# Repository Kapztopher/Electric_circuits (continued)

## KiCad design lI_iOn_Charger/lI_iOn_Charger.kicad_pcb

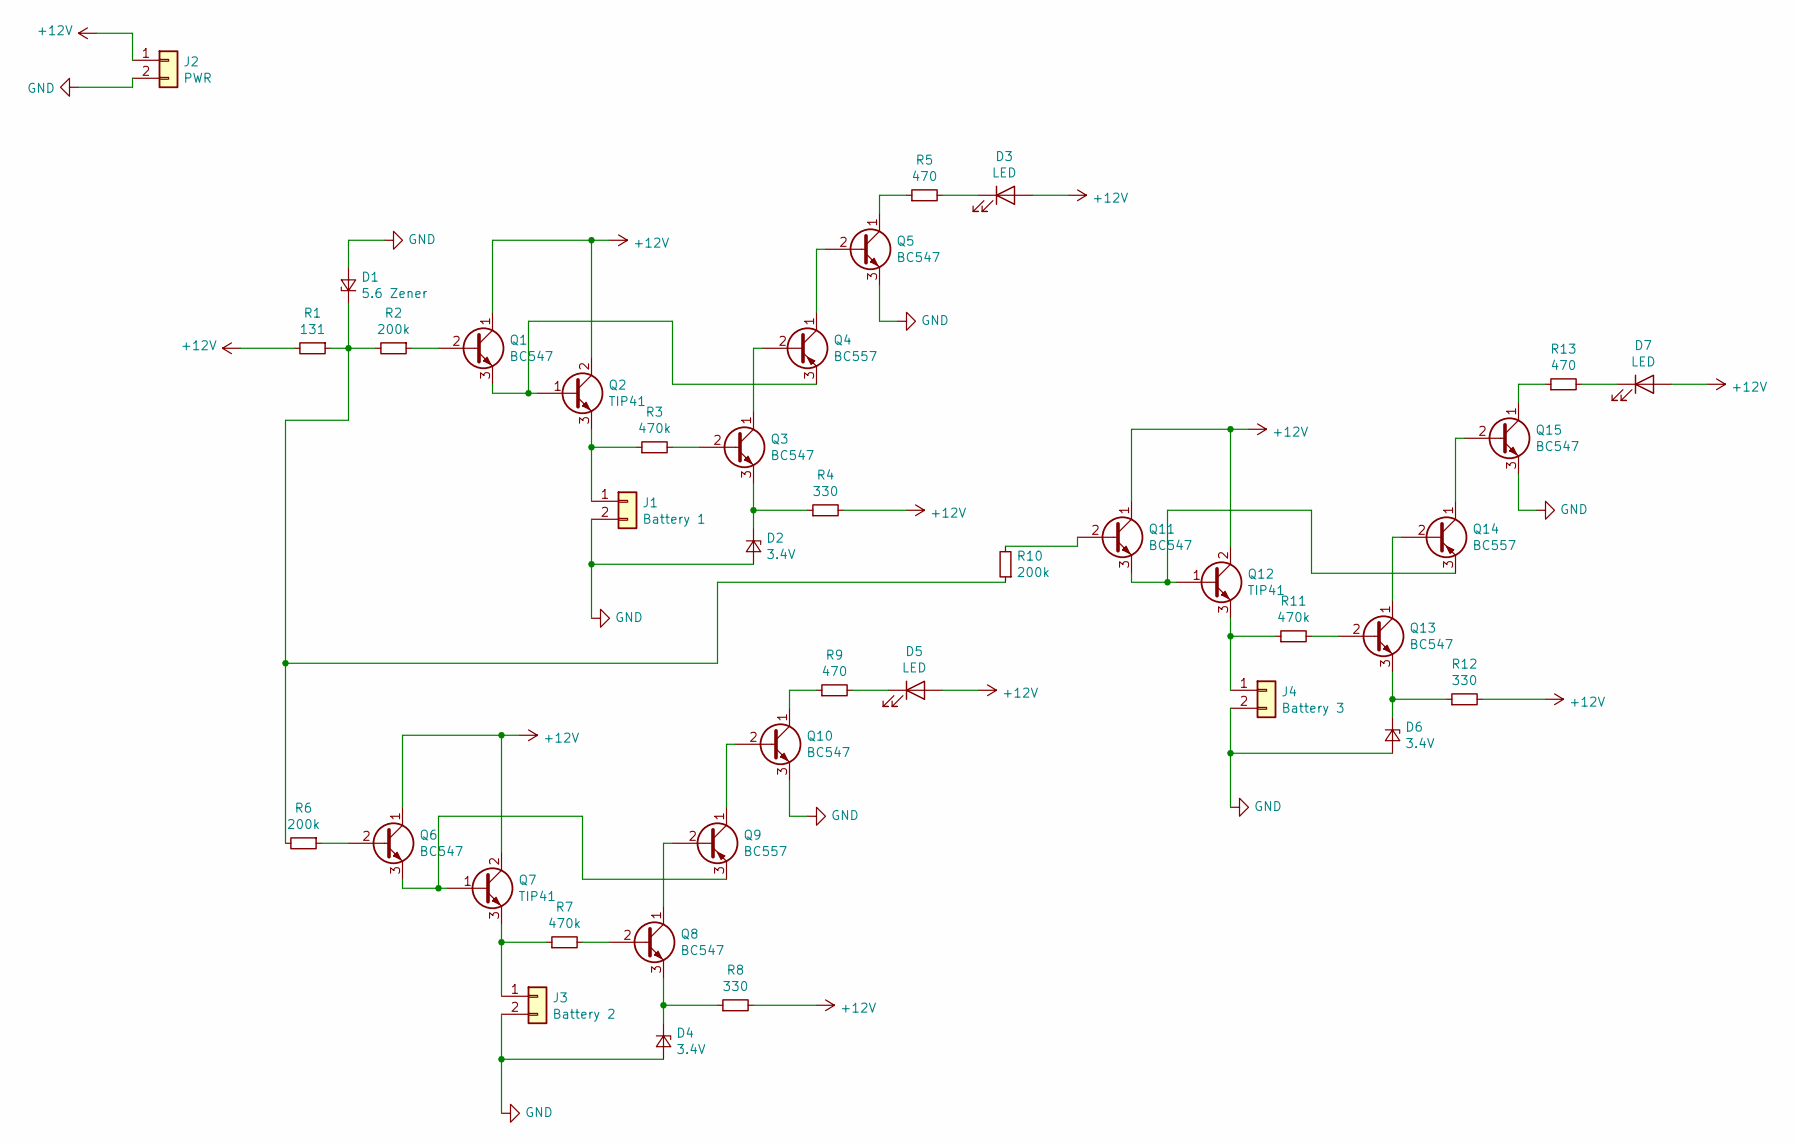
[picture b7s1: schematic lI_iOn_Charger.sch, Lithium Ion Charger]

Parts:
D1: 5.6 Zener; D_DO-41_SOD81_P7.62mm_Horizontal
D2, D4, D6: 3.4V; D_DO-41_SOD81_P7.62mm_Horizontal
D3, D5, D7: LED; LED_D5.0mm
J1: Battery 1; PinHeader_1x02_P2.54mm_Vertical
J2: PWR; PinHeader_1x02_P2.54mm_Vertical
J3: Battery 2; PinHeader_1x02_P2.54mm_Vertical
J4: Battery 3; PinHeader_1x02_P2.54mm_Vertical
Q1, Q3, Q5, Q6, Q8, Q10, Q11, Q13, Q15: BC547; TO-92_HandSolder
Q2, Q7, Q12: TIP41; TO-220-3_Vertical
Q4, Q9, Q14: BC557; TO-92_HandSolder
R1: 131; R_Axial_DIN0207_L6.3mm_D2.5mm_P7.62mm_Horizontal
R2, R6, R10: 200k; R_Axial_DIN0207_L6.3mm_D2.5mm_P7.62mm_Horizontal
R3, R7, R11: 470k; R_Axial_DIN0207_L6.3mm_D2.5mm_P7.62mm_Horizontal
R4, R8, R12: 330; R_Axial_DIN0207_L6.3mm_D2.5mm_P7.62mm_Horizontal
R5, R9, R13: 470; R_Axial_DIN0207_L6.3mm_D2.5mm_P7.62mm_Horizontal

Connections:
+12V: D3.2 (A), D5.2 (A), D7.2 (A), J2.1, Q1.1 (C), Q2.2 (C), Q6.1 (C), Q7.2 (C), Q11.1 (C), Q12.2 (C), R1.2, R4.2, R8.2, R12.2
GND: D1.2 (A), D2.2 (A), D4.2 (A), D6.2 (A), J1.2, J2.2, J3.2, J4.2, Q5.3 (E), Q10.3 (E), Q15.3 (E)
unnamed: D1.1 (K), R1.1, R2.2, R6.2, R10.1
unnamed: D2.1 (K), Q3.3 (E), R4.1
unnamed: D3.1 (K), R5.2
unnamed: D4.1 (K), Q8.3 (E), R8.1
unnamed: D5.1 (K), R9.2
unnamed: D6.1 (K), Q13.3 (E), R12.1
unnamed: D7.1 (K), R13.2
unnamed: J1.1, Q2.3 (E), R3.1
unnamed: J3.1, Q7.3 (E), R7.1
unnamed: J4.1, Q12.3 (E), R11.1
unnamed: Q1.2 (B), R2.1
unnamed: Q1.3 (E), Q2.1 (B), Q4.3 (E)
unnamed: Q3.1 (C), Q4.2 (B)
unnamed: Q3.2 (B), R3.2
unnamed: Q4.1 (C), Q5.2 (B)
unnamed: Q5.1 (C), R5.1
unnamed: Q6.2 (B), R6.1
unnamed: Q6.3 (E), Q7.1 (B), Q9.3 (E)
unnamed: Q8.1 (C), Q9.2 (B)
unnamed: Q8.2 (B), R7.2
unnamed: Q10.1 (C), R9.1
unnamed: Q9.1 (C), Q10.2 (B)
unnamed: Q11.2 (B), R10.2
unnamed: Q11.3 (E), Q12.1 (B), Q14.3 (E)
unnamed: Q13.1 (C), Q14.2 (B)
unnamed: Q13.2 (B), R11.2
unnamed: Q14.1 (C), Q15.2 (B)
unnamed: Q15.1 (C), R13.1

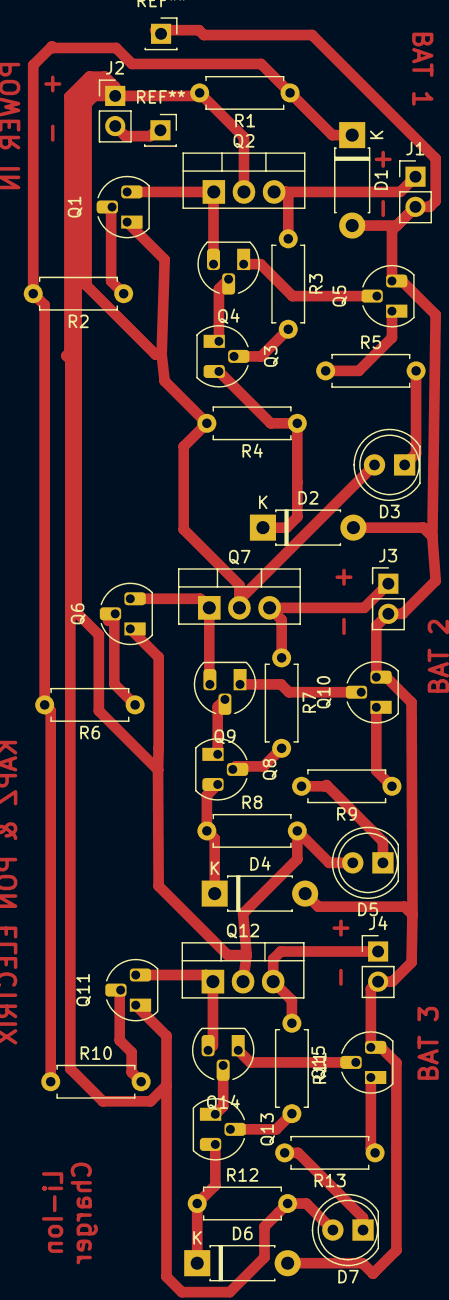
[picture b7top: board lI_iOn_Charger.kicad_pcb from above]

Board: 2 copper layers, 39 parts (0 on the bottom side), 30 nets.

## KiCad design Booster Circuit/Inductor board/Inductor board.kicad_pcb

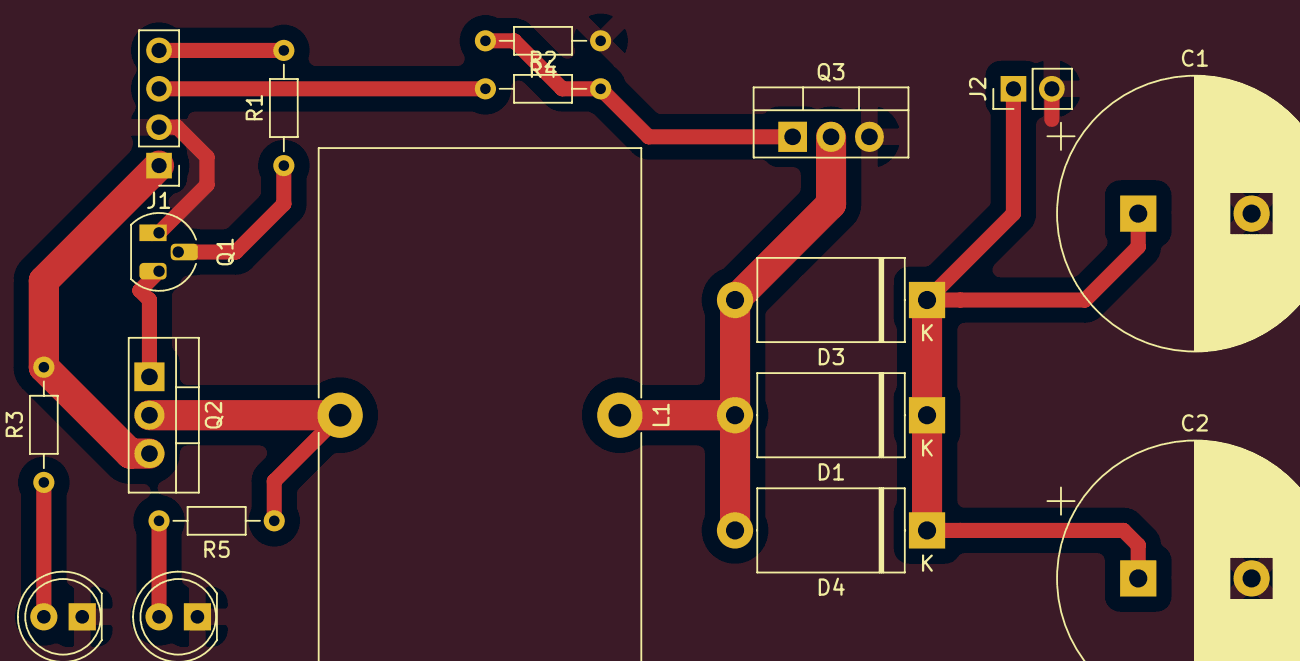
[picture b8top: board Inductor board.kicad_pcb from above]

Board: 2 copper layers, 18 parts (0 on the bottom side), 12 nets.

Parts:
C1, C2: 250V +; CP_Radial_D18.0mm_P7.50mm
D1, D3, D4: D_Schottky; D_DO-27_P12.70mm_Horizontal
D2, D5: LED; LED_D5.0mm
J1: PWR_EN_PWM; PinHeader_1x04_P2.54mm_Vertical
J2: PWR OUT; PinHeader_1x02_P2.54mm_Vertical
L1: L; L_Toroid_Vertical_L35.1mm_W21.1mm_P18.50mm_Vishay_TJ6
Q1: PN100; TO-92_HandSolder_PN?00
Q2: TIP42C; TO-220-3_Vertical
Q3: IRF540N; TO-220-3_Vertical
R1: 610K; R_Axial_DIN0204_L3.6mm_D1.6mm_P7.62mm_Horizontal
R2: 700; R_Axial_DIN0204_L3.6mm_D1.6mm_P7.62mm_Horizontal
R3, R5: 625; R_Axial_DIN0204_L3.6mm_D1.6mm_P7.62mm_Horizontal
R4: 70K; R_Axial_DIN0204_L3.6mm_D1.6mm_P7.62mm_Horizontal

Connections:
+VDC: J1.1, Q2.3, R3.2
GND: C1.2, C2.2, D2.1, D5.1, J1.2, J2.2, Q1.1, Q3.3, R4.1
unnamed: C1.1, C2.1, D1.1, D3.1, D4.1, J2.1
unnamed: D1.2, D3.2, D4.2, L1.1, Q3.2
unnamed: D2.2, R3.1
unnamed: D5.2, R5.2
unnamed: J1.3, R2.1
unnamed: J1.4, R1.2
unnamed: L1.2, Q2.2, R5.1
unnamed: Q1.2, R1.1
unnamed: Q1.3, Q2.1
unnamed: Q3.1, R2.2, R4.2

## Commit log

2022-09-08 Various electronic circuits
2022-09-25 Deleted unwanted backup files and change directory names to easier top use and understand names
2022-09-25 Addded ReadMe.txt files to aid use, and deleted missed backup files
2022-09-26 Added note to graphics equliser display PCB
